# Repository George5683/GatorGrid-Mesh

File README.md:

# GatorGrid

GatorGrid is a multifunctional software solution designed for the Raspberry Pi Pico W by UF students to create a mesh network with wireless communication. It provides a low-cost, open-source alternative to existing mesh network solutions like ESP-WIFI-MESH and Zigbee by enabling seamless Wi-Fi-based communication between multiple nodes. The design uses two Pico W's per node in the network The project aims to ensure reliable message relay, even in case of node failures, making it ideal for individuals and organizations needing decentralized communication in remote or disaster-affected areas. GatorGrid focuses on accessibility, scalability, and real-time data transmission.

## Features
- MeshNode library for STA and AP mode
- Doxygen for documentation
- UART interaction for internode communication
- Kicad Custom PCB deisgn with external battery charging capabilities
- Network tree based creation from designated root node

## Requirements to run
- Install doxygen
- Install graphviz
- Install extensions for VS code if applicable: Doxygen Documentation Generator 

## How to run Doxygen
1. Use doxygen Doxyfile to generate the documentation
2. Use **start doc\html\index.html** (WINDOWS ONLY) or **open doc/html/index.html** (LINUX/MAC)

## How to upload code to PICO W's
1. Push the bootsel and plug the microcontroller into the computer
2. Create the .uf2 file and upload it to PICO W by dragging it into the directory

# PCB
The PCB is deisgned to have two Pico W's connected to each of the two vertical slots.

## Bugs:
- At the moment if in an environment with high congestion, packets may not arrive. Moving locations is required.
- SPI has a slight delay of 110 ms per message sent. 

## Author
George Salomon, Cole Smith, Jonathon Brown, Mateo Slivka, Maxwell Evans

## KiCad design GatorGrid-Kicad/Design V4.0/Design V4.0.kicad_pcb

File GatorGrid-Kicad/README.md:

## Kicad Designs

Design are separated into versions based on functionality and Design stages 

*Starting from BETA BUILD the first design V(X.0) is always the dev kit with extra Pico pinouts sockets for monitoring*

# Kicad Stages      
- INITIAL BUILD (V0.1 & V1.0)
- ALPHA BUILD (V2.0+)
- BETA BUILD (V3.0+)
- FINAL BUILD (V4.0+)

# External Sensor
At the moment the external sensor list is limited but can be expanded as needed
- DHT11 external PCB extension

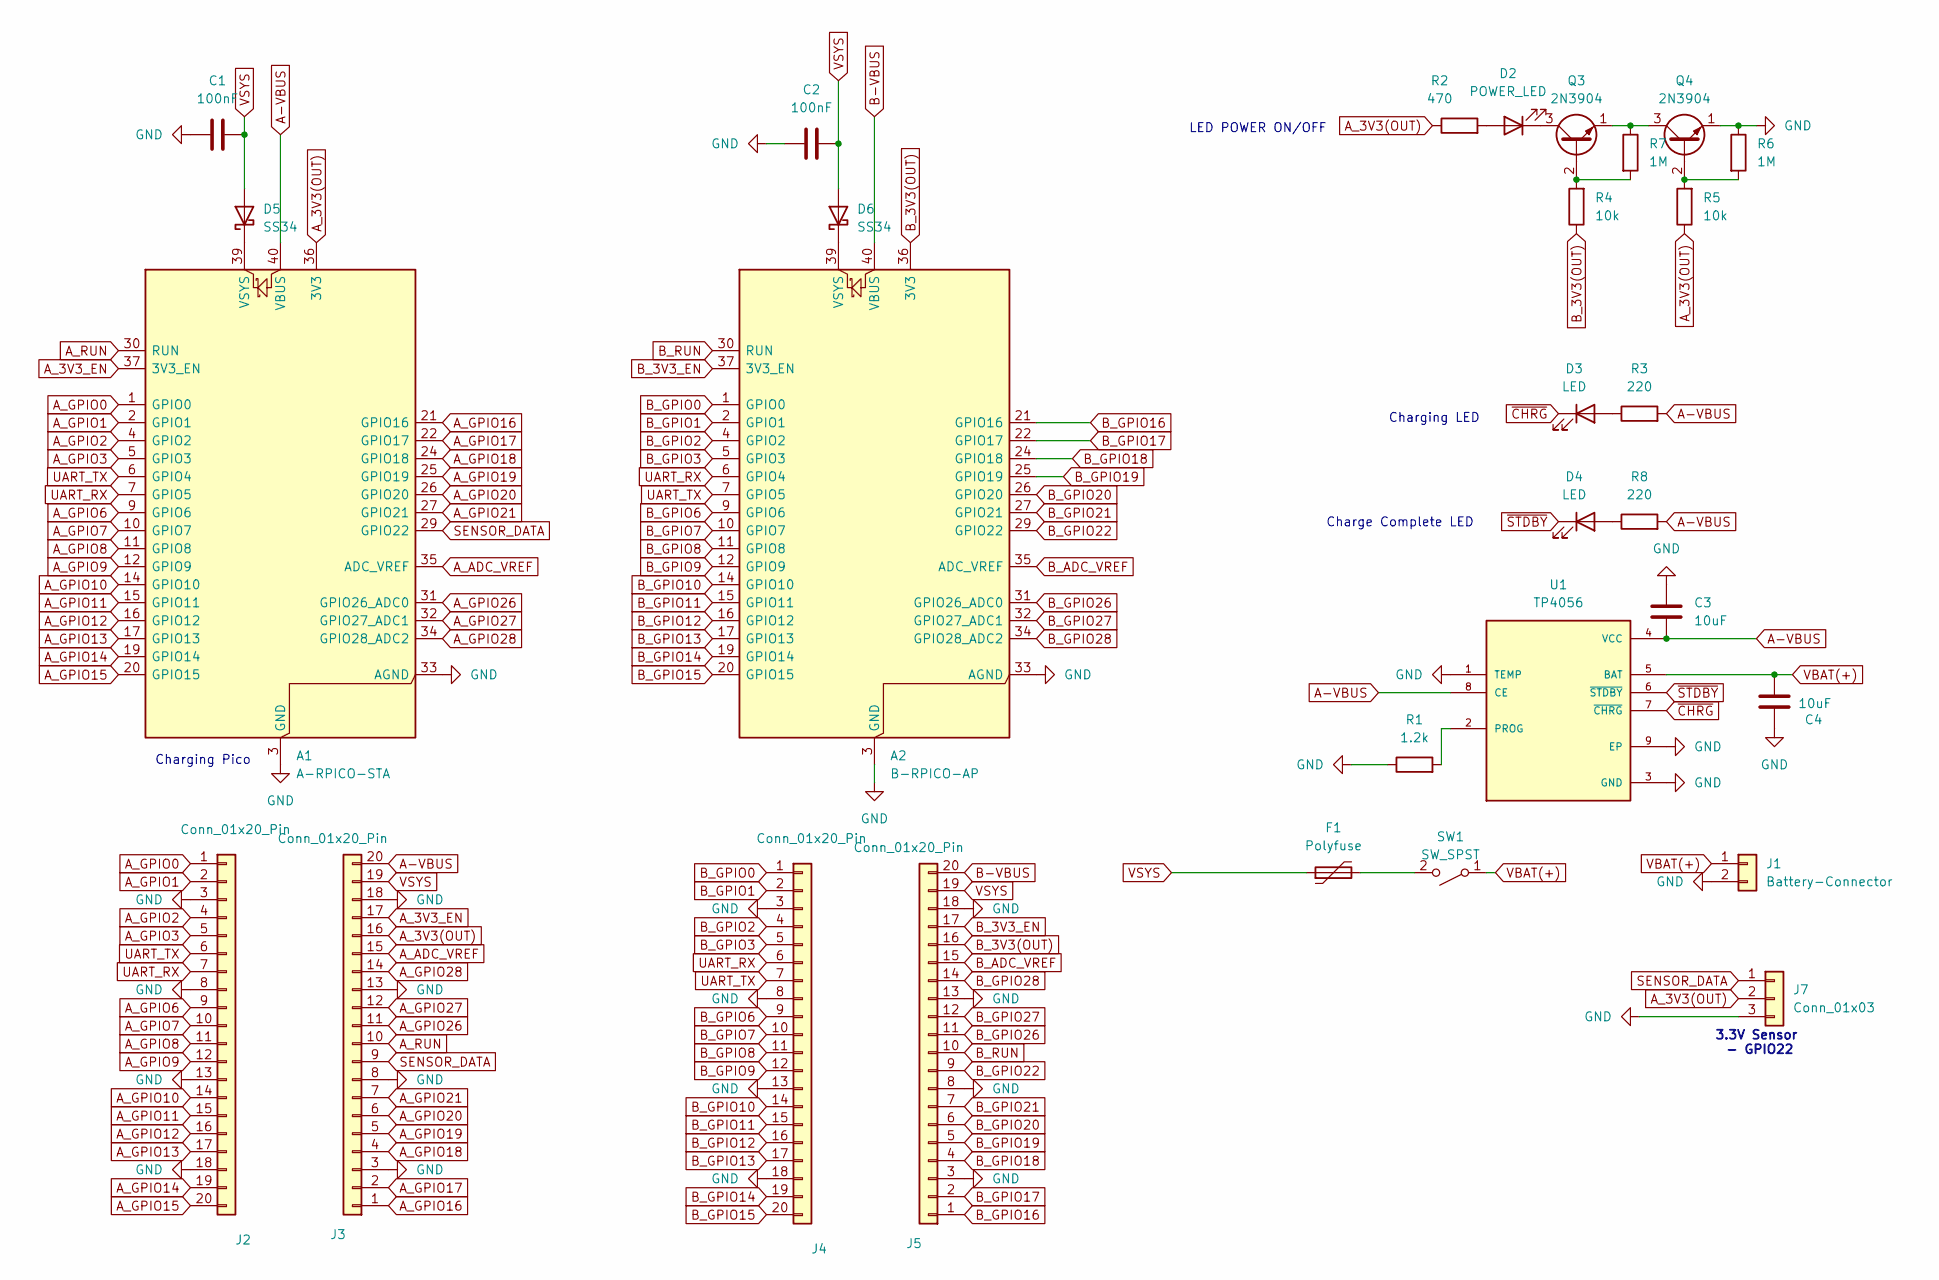
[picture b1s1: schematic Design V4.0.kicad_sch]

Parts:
A1: A-RPICO-STA; RaspberryPi_Pico_Common_THT
A2: B-RPICO-AP; RaspberryPi_Pico_Common_THT
C1, C2: 100nF; C_Disc_D5.0mm_W2.5mm_P2.50mm
C3, C4: 10uF; C_Radial_D5.0mm_H11.0mm_P2.00mm
D2: POWER_LED; LED_D5.0mm
D3, D4: LED; LED_D5.0mm
D5, D6: SS34; D_DO-41_SOD81_P7.62mm_Horizontal
F1: Polyfuse; Fuse_BelFuse_0ZRE0005FF_L8.3mm_W3.8mm
J1: Battery-Connector; JST_PH_S2B-PH-K_1x02_P2.00mm_Horizontal
J2, J3, J4, J5: Conn_01x20_Pin; PinSocket_1x20_P2.54mm_Vertical
J7: Conn_01x03; JST_XH_S3B-XH-A_1x03_P2.50mm_Horizontal
Q3, Q4: 2N3904; TO-92_Inline
R1: 1.2k; R_Axial_DIN0207_L6.3mm_D2.5mm_P7.62mm_Horizontal
R2: 470; R_Axial_DIN0207_L6.3mm_D2.5mm_P7.62mm_Horizontal
R3, R8: 220; R_Axial_DIN0207_L6.3mm_D2.5mm_P7.62mm_Horizontal
R4, R5: 10k; R_Axial_DIN0207_L6.3mm_D2.5mm_P7.62mm_Horizontal
R6, R7: 1M; R_Axial_DIN0207_L6.3mm_D2.5mm_P7.62mm_Horizontal
SW1: SW_SPST; SW_Slide_SPDT_Angled_CK_OS102011MA1Q
U1: TP4056; SOP127P600X175-9N

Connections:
A-VBUS: A1.40 (VBUS), C3.2, J3.20, R3.2, R8.2, U1.4 (VCC), U1.8 (CE)
A_3V3(OUT): A1.36 (3V3), J3.16, J7.2, R2.1, R5.1
A_3V3_EN: A1.37 (3V3_EN), J3.17
A_ADC_VREF: A1.35 (ADC_VREF), J3.15
A_GPIO0: A1.1 (GPIO0), J2.1
A_GPIO1: A1.2 (GPIO1), J2.2
A_GPIO2: A1.4 (GPIO2), J2.4
A_GPIO3: A1.5 (GPIO3), J2.5
A_GPIO6: A1.9 (GPIO6), J2.9
A_GPIO7: A1.10 (GPIO7), J2.10
A_GPIO8: A1.11 (GPIO8), J2.11
A_GPIO9: A1.12 (GPIO9), J2.12
A_GPIO10: A1.14 (GPIO10), J2.14
A_GPIO11: A1.15 (GPIO11), J2.15
A_GPIO12: A1.16 (GPIO12), J2.16
A_GPIO13: A1.17 (GPIO13), J2.17
A_GPIO14: A1.19 (GPIO14), J2.19
A_GPIO15: A1.20 (GPIO15), J2.20
A_GPIO16: A1.21 (GPIO16), J3.1
A_GPIO17: A1.22 (GPIO17), J3.2
A_GPIO18: A1.24 (GPIO18), J3.4
A_GPIO19: A1.25 (GPIO19), J3.5
A_GPIO20: A1.26 (GPIO20), J3.6
A_GPIO21: A1.27 (GPIO21), J3.7
A_GPIO26: A1.31 (GPIO26_ADC0), J3.11
A_GPIO27: A1.32 (GPIO27_ADC1), J3.12
A_GPIO28: A1.34 (GPIO28_ADC2), J3.14
A_RUN: A1.30 (RUN), J3.10
B-VBUS: A2.40 (VBUS), J5.20
B_3V3(OUT): A2.36 (3V3), J5.16, R4.1
B_3V3_EN: A2.37 (3V3_EN), J5.17
B_ADC_VREF: A2.35 (ADC_VREF), J5.15
B_GPIO0: A2.1 (GPIO0), J4.1
B_GPIO1: A2.2 (GPIO1), J4.2
B_GPIO2: A2.4 (GPIO2), J4.4
B_GPIO3: A2.5 (GPIO3), J4.5
B_GPIO6: A2.9 (GPIO6), J4.9
B_GPIO7: A2.10 (GPIO7), J4.10
B_GPIO8: A2.11 (GPIO8), J4.11
B_GPIO9: A2.12 (GPIO9), J4.12
B_GPIO10: A2.14 (GPIO10), J4.14
B_GPIO11: A2.15 (GPIO11), J4.15
B_GPIO12: A2.16 (GPIO12), J4.16
B_GPIO13: A2.17 (GPIO13), J4.17
B_GPIO14: A2.19 (GPIO14), J4.19
B_GPIO15: A2.20 (GPIO15), J4.20
B_GPIO16: A2.21 (GPIO16), J5.1
B_GPIO17: A2.22 (GPIO17), J5.2
B_GPIO18: A2.24 (GPIO18), J5.4
B_GPIO19: A2.25 (GPIO19), J5.5
B_GPIO20: A2.26 (GPIO20), J5.6
B_GPIO21: A2.27 (GPIO21), J5.7
B_GPIO22: A2.29 (GPIO22), J5.9
B_GPIO26: A2.31 (GPIO26_ADC0), J5.11
B_GPIO27: A2.32 (GPIO27_ADC1), J5.12
B_GPIO28: A2.34 (GPIO28_ADC2), J5.14
B_RUN: A2.30 (RUN), J5.10
GND: A1.3 (GND), A1.8 (GND), A1.13 (GND), A1.18 (GND), A1.23 (GND), A1.28 (GND), A1.33 (AGND), A1.38 (GND), A2.3 (GND), A2.8 (GND), A2.13 (GND), A2.18 (GND), A2.23 (GND), A2.28 (GND), A2.33 (AGND), A2.38 (GND), C1.2, C2.1, C3.1, C4.1, J1.2, J2.3, J2.8, J2.13, J2.18, J3.3, J3.8, J3.13, J3.18, J4.3, J4.8, J4.13, J4.18, J5.3, J5.8, J5.13, J5.18, J7.3, Q4.1 (E), R1.1, R6.1, U1.1 (TEMP), U1.3 (GND), U1.9 (EP)
unnamed: A1.39 (VSYS), D5.1 (K)
unnamed: A2.39 (VSYS), D6.1 (K)
unnamed: D2.2 (A), R2.2
unnamed: D2.1 (K), Q3.3 (C)
unnamed: D3.2 (A), R3.1
unnamed: D4.2 (A), R8.1
unnamed: Q3.2 (B), R4.2, R7.2
unnamed: Q3.1 (E), Q4.3 (C), R7.1
unnamed: Q4.2 (B), R5.2, R6.2
unnamed: F1.2, SW1.2 (B)
unnamed: R1.2, U1.2 (PROG)
SENSOR_DATA: A1.29 (GPIO22), J3.9, J7.1
UART_RX: A1.7 (GPIO5), A2.6 (GPIO4), J2.7, J4.6
UART_TX: A1.6 (GPIO4), A2.7 (GPIO5), J2.6, J4.7
VBAT(+): C4.2, J1.1, SW1.1 (A), U1.5 (BAT)
VSYS: C1.1, C2.2, D5.2 (A), D6.2 (A), F1.1, J3.19, J5.19
~CHRG: D3.1 (K), U1.7 (~CHRG)
~STDBY: D4.1 (K), U1.6 (~STDBY)

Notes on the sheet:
Charging Pico
Charge Complete LED
3.3V Sensor - GPIO22
LED POWER ON/OFF
Charging LED

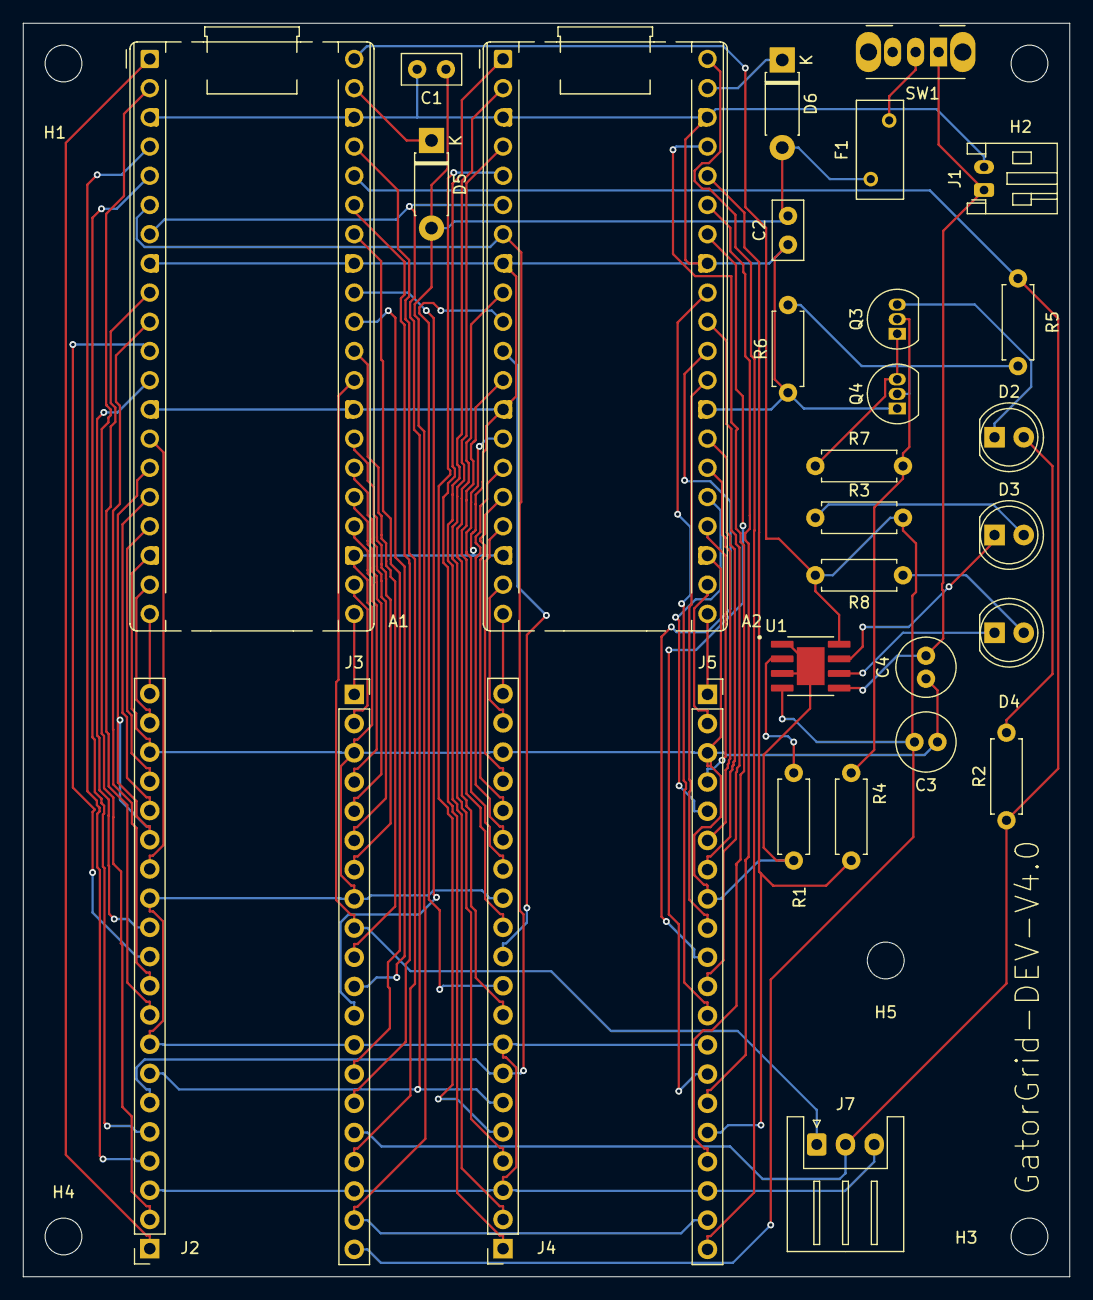
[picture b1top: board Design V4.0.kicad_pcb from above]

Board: 2 copper layers, 91.0 x 109.0 mm, 35 parts (0 on the bottom side), 76 nets.

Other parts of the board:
H1, H2, H3, H4, H5: MountingHole_3.2mm_M3_ISO7380

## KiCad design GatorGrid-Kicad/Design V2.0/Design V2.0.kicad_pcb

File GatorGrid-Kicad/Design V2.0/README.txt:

# Kicad Design V2.0

## Explanation for the Pinouts on the Pico W:

- GPIO 1-22 and 26-28 are as the schematic states
- VBUS is 5V when connected to micro usb to power the Pico
- VSYS can power the Pico with ~1.8-5.5V input

## Schematic Update:
- Fixed wiring of temp on the TP4056 as it was disconnected which casued the battery to not charge. 
- Changed POWER LED to be driven by two transistors which allows it to turn on when both picos are on. 
- Removed the schottky diode connected to the battery and instead put a diode on each VSYS out from each pico in order to prevent backflow when eitehr are plugged in as VSYS can be input and output. 
- Reworked Wiring on PCB

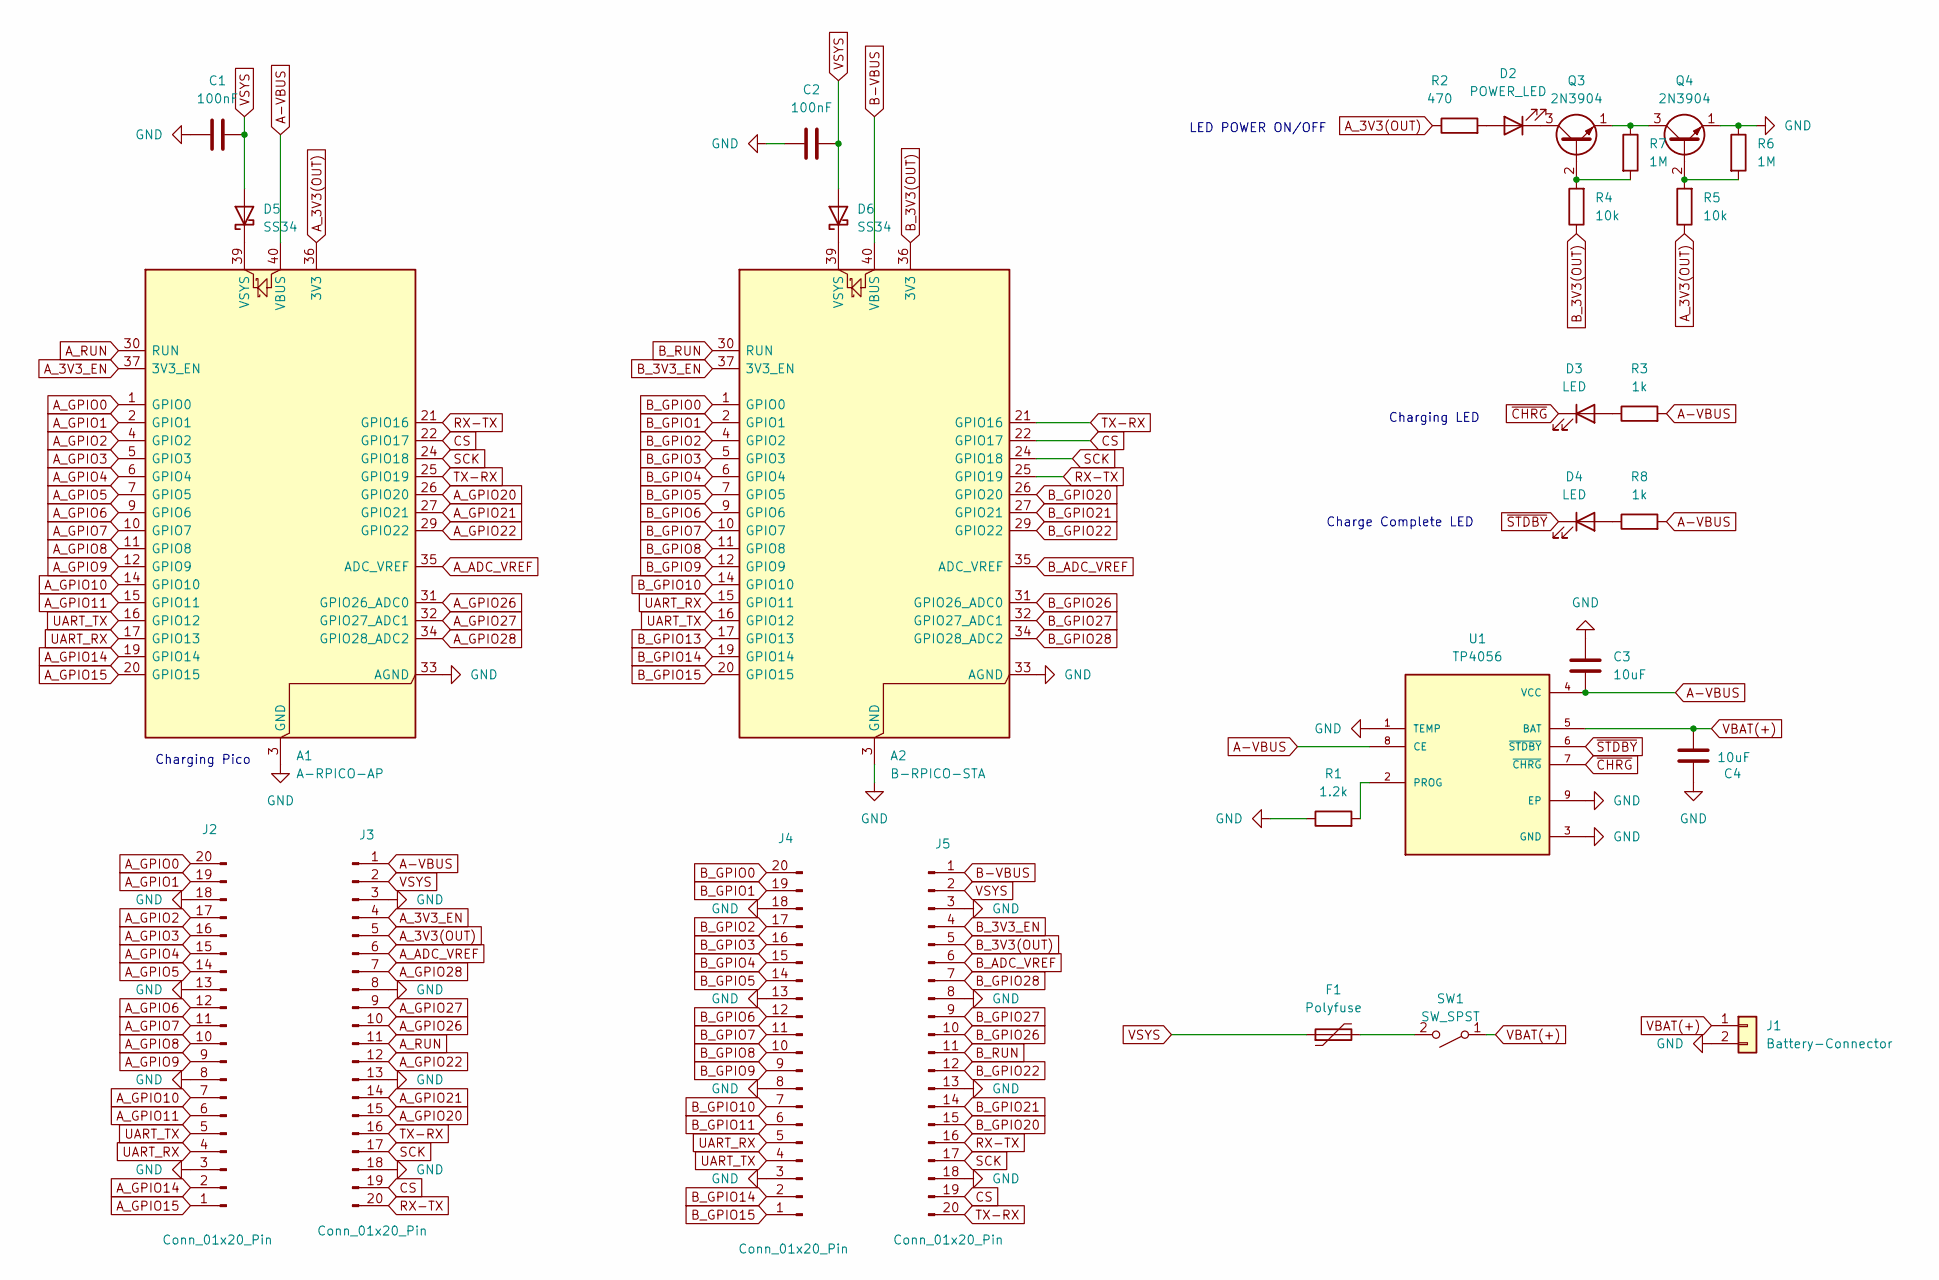
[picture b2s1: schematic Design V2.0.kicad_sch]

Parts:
A1: A-RPICO-AP; RaspberryPi_Pico_Common_THT
A2: B-RPICO-STA; RaspberryPi_Pico_Common_THT
C1, C2: 100nF; C_Disc_D5.0mm_W2.5mm_P2.50mm
C3, C4: 10uF; C_Radial_D5.0mm_H11.0mm_P2.00mm
D2: POWER_LED; LED_D5.0mm
D3, D4: LED; LED_D5.0mm
D5, D6: SS34; D_DO-41_SOD81_P7.62mm_Horizontal
F1: Polyfuse; Fuse_BelFuse_0ZRE0005FF_L8.3mm_W3.8mm
J1: Battery-Connector; JST_PH_S2B-PH-K_1x02_P2.00mm_Horizontal
J2, J3, J4, J5: Conn_01x20_Pin; PinSocket_1x20_P2.54mm_Vertical
Q3, Q4: 2N3904; TO-92_Inline
R1: 1.2k; R_Axial_DIN0207_L6.3mm_D2.5mm_P7.62mm_Horizontal
R2: 470; R_Axial_DIN0207_L6.3mm_D2.5mm_P7.62mm_Horizontal
R3, R8: 1k; R_Axial_DIN0207_L6.3mm_D2.5mm_P7.62mm_Horizontal
R4, R5: 10k; R_Axial_DIN0207_L6.3mm_D2.5mm_P7.62mm_Horizontal
R6, R7: 1M; R_Axial_DIN0207_L6.3mm_D2.5mm_P7.62mm_Horizontal
SW1: SW_SPST; SW_Slide_SPDT_Angled_CK_OS102011MA1Q
U1: TP4056; SOP127P600X175-9N

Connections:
A-VBUS: A1.40 (VBUS), C3.2, J3.1, R3.2, R8.2, U1.4 (VCC), U1.8 (CE)
A_3V3(OUT): A1.36 (3V3), J3.5, R2.1, R5.1
A_3V3_EN: A1.37 (3V3_EN), J3.4
A_ADC_VREF: A1.35 (ADC_VREF), J3.6
A_GPIO0: A1.1 (GPIO0), J2.20
A_GPIO1: A1.2 (GPIO1), J2.19
A_GPIO2: A1.4 (GPIO2), J2.17
A_GPIO3: A1.5 (GPIO3), J2.16
A_GPIO4: A1.6 (GPIO4), J2.15
A_GPIO5: A1.7 (GPIO5), J2.14
A_GPIO6: A1.9 (GPIO6), J2.12
A_GPIO7: A1.10 (GPIO7), J2.11
A_GPIO8: A1.11 (GPIO8), J2.10
A_GPIO9: A1.12 (GPIO9), J2.9
A_GPIO10: A1.14 (GPIO10), J2.7
A_GPIO11: A1.15 (GPIO11), J2.6
A_GPIO14: A1.19 (GPIO14), J2.2
A_GPIO15: A1.20 (GPIO15), J2.1
A_GPIO20: A1.26 (GPIO20), J3.15
A_GPIO21: A1.27 (GPIO21), J3.14
A_GPIO22: A1.29 (GPIO22), J3.12
A_GPIO26: A1.31 (GPIO26_ADC0), J3.10
A_GPIO27: A1.32 (GPIO27_ADC1), J3.9
A_GPIO28: A1.34 (GPIO28_ADC2), J3.7
A_RUN: A1.30 (RUN), J3.11
B-VBUS: A2.40 (VBUS), J5.1
B_3V3(OUT): A2.36 (3V3), J5.5, R4.1
B_3V3_EN: A2.37 (3V3_EN), J5.4
B_ADC_VREF: A2.35 (ADC_VREF), J5.6
B_GPIO0: A2.1 (GPIO0), J4.20
B_GPIO1: A2.2 (GPIO1), J4.19
B_GPIO2: A2.4 (GPIO2), J4.17
B_GPIO3: A2.5 (GPIO3), J4.16
B_GPIO4: A2.6 (GPIO4), J4.15
B_GPIO5: A2.7 (GPIO5), J4.14
B_GPIO6: A2.9 (GPIO6), J4.12
B_GPIO7: A2.10 (GPIO7), J4.11
B_GPIO8: A2.11 (GPIO8), J4.10
B_GPIO9: A2.12 (GPIO9), J4.9
B_GPIO10: A2.14 (GPIO10), J4.7
B_GPIO11: J4.6
B_GPIO13: A2.17 (GPIO13)
B_GPIO14: A2.19 (GPIO14), J4.2
B_GPIO15: A2.20 (GPIO15), J4.1
B_GPIO20: A2.26 (GPIO20), J5.15
B_GPIO21: A2.27 (GPIO21), J5.14
B_GPIO22: A2.29 (GPIO22), J5.12
B_GPIO26: A2.31 (GPIO26_ADC0), J5.10
B_GPIO27: A2.32 (GPIO27_ADC1), J5.9
B_GPIO28: A2.34 (GPIO28_ADC2), J5.7
B_RUN: A2.30 (RUN), J5.11
CS: A1.22 (GPIO17), A2.22 (GPIO17), J3.19, J5.19
GND: A1.3 (GND), A1.8 (GND), A1.13 (GND), A1.18 (GND), A1.23 (GND), A1.28 (GND), A1.33 (AGND), A1.38 (GND), A2.3 (GND), A2.8 (GND), A2.13 (GND), A2.18 (GND), A2.23 (GND), A2.28 (GND), A2.33 (AGND), A2.38 (GND), C1.2, C2.1, C3.1, C4.1, J1.2, J2.3, J2.8, J2.13, J2.18, J3.3, J3.8, J3.13, J3.18, J4.3, J4.8, J4.13, J4.18, J5.3, J5.8, J5.13, J5.18, Q4.1 (E), R1.1, R6.1, U1.1 (TEMP), U1.3 (GND), U1.9 (EP)
unnamed: A1.39 (VSYS), D5.1 (K)
unnamed: A2.39 (VSYS), D6.1 (K)
unnamed: D2.2 (A), R2.2
unnamed: D2.1 (K), Q3.3 (C)
unnamed: D3.2 (A), R3.1
unnamed: D4.2 (A), R8.1
unnamed: Q3.2 (B), R4.2, R7.2
unnamed: Q3.1 (E), Q4.3 (C), R7.1
unnamed: Q4.2 (B), R5.2, R6.2
unnamed: F1.2, SW1.2 (B)
unnamed: R1.2, U1.2 (PROG)
RX-TX: A1.21 (GPIO16), A2.25 (GPIO19), J3.20, J5.16
SCK: A1.24 (GPIO18), A2.24 (GPIO18), J3.17, J5.17
TX-RX: A1.25 (GPIO19), A2.21 (GPIO16), J3.16, J5.20
UART_RX: A1.17 (GPIO13), A2.15 (GPIO11), J2.4, J4.5
UART_TX: A1.16 (GPIO12), A2.16 (GPIO12), J2.5, J4.4
VBAT(+): C4.2, J1.1, SW1.1 (A), U1.5 (BAT)
VSYS: C1.1, C2.2, D5.2 (A), D6.2 (A), F1.1, J3.2, J5.2
~CHRG: D3.1 (K), U1.7 (~CHRG)
~STDBY: D4.1 (K), U1.6 (~STDBY)

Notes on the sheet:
Charging Pico
Charge Complete LED
LED POWER ON/OFF
Charging LED

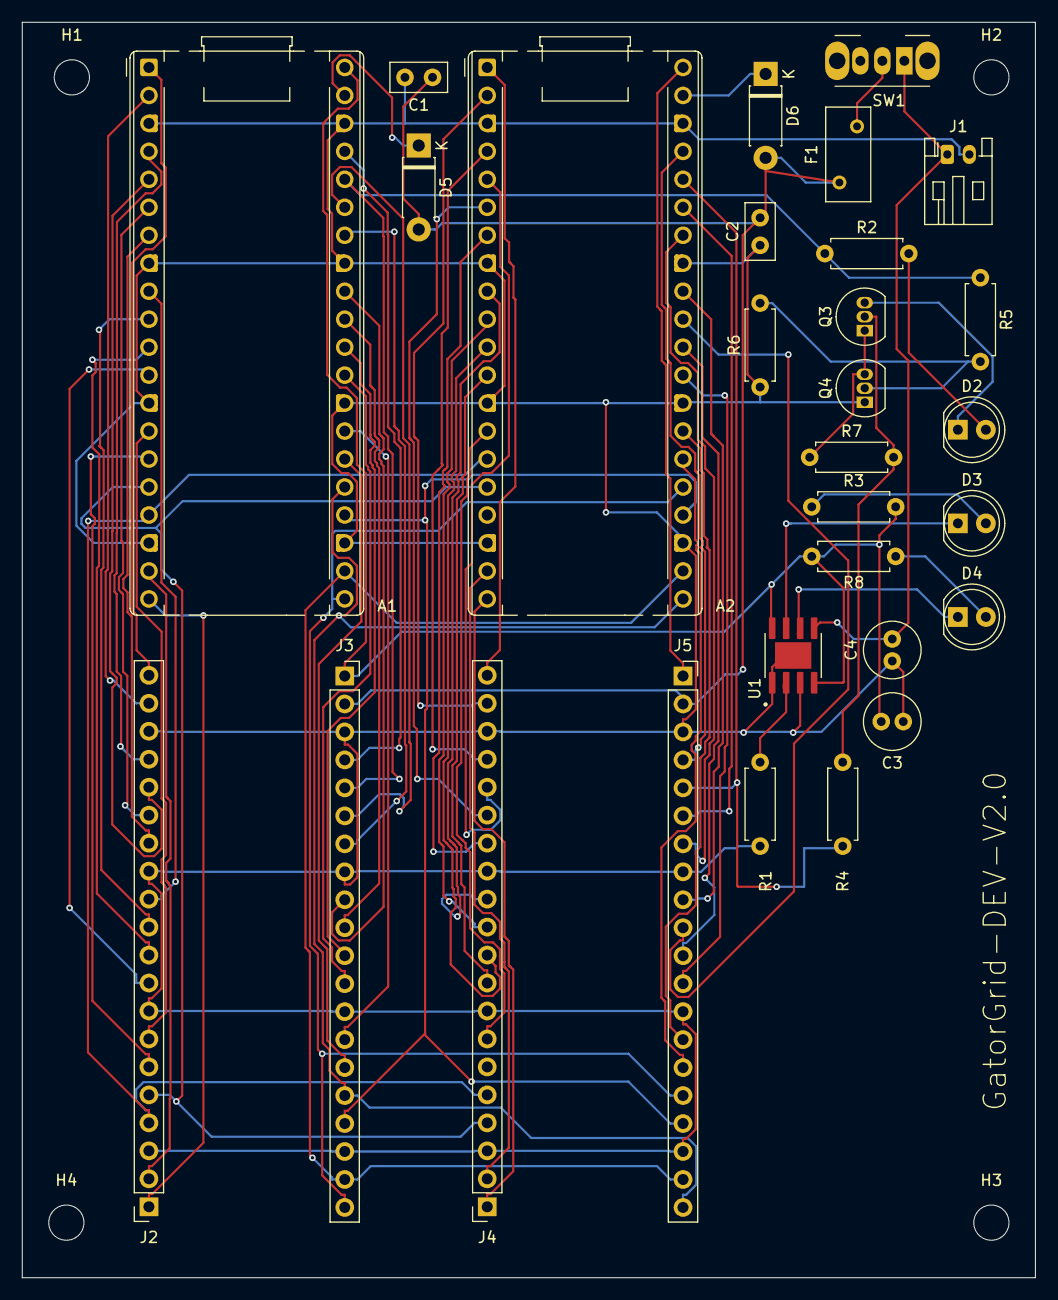
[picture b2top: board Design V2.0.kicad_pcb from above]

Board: 2 copper layers, 92.0 x 114.0 mm, 33 parts (0 on the bottom side), 71 nets.

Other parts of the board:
H1, H2, H3, H4: MountingHole_3.2mm_M3_ISO7380

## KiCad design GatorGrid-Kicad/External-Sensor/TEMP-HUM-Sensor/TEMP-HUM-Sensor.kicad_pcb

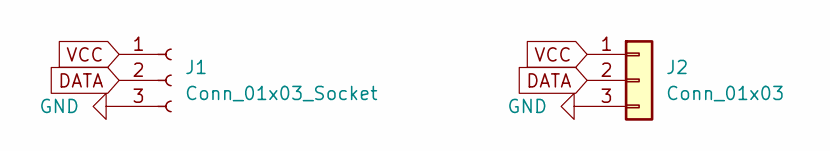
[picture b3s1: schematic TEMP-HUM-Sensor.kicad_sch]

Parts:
J1: Conn_01x03_Socket; PinSocket_1x03_P2.54mm_Vertical
J2: Conn_01x03; JST_XH_S3B-XH-A_1x03_P2.50mm_Horizontal

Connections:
DATA: J1.2, J2.2
GND: J1.3, J2.3
VCC: J1.1, J2.1

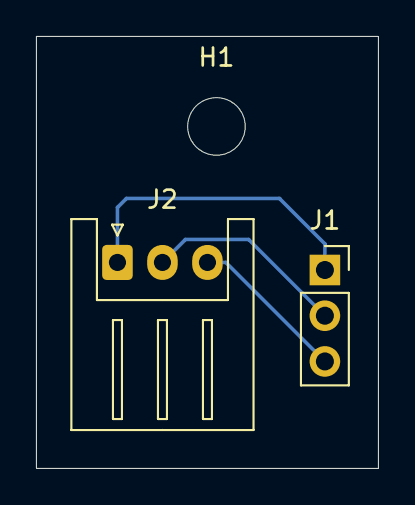
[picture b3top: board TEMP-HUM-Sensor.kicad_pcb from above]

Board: 2 copper layers, 19.0 x 24.0 mm, 3 parts (0 on the bottom side), 3 nets.

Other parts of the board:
H1: MountingHole_3.2mm_M3_ISO7380

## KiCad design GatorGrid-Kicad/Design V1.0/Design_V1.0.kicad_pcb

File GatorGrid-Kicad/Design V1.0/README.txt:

# Kicad Design V1.0

## Explanation for the Pinouts on the Pico W:

- GPIO 1-22 and 26-28 are as the schematic states
- VBUS is 5V when connected to micro usb to power the Pico
- VSYS can power the Pico with ~1.8-5.5V input

## Schematic Update:
- Added a JST connector for an extenal battery to be connected
- Added a switch after the JSt conncector for powering the Picos
- Added a polyfuse (polyfuse's reset instead of replacing the fuse if its broken)
- Added a Schottky diode (to prevent current backflow and if user connects the battery backwards)
- Added a charging/safety cicuit [TP4056] (for charging the battery and battery management)

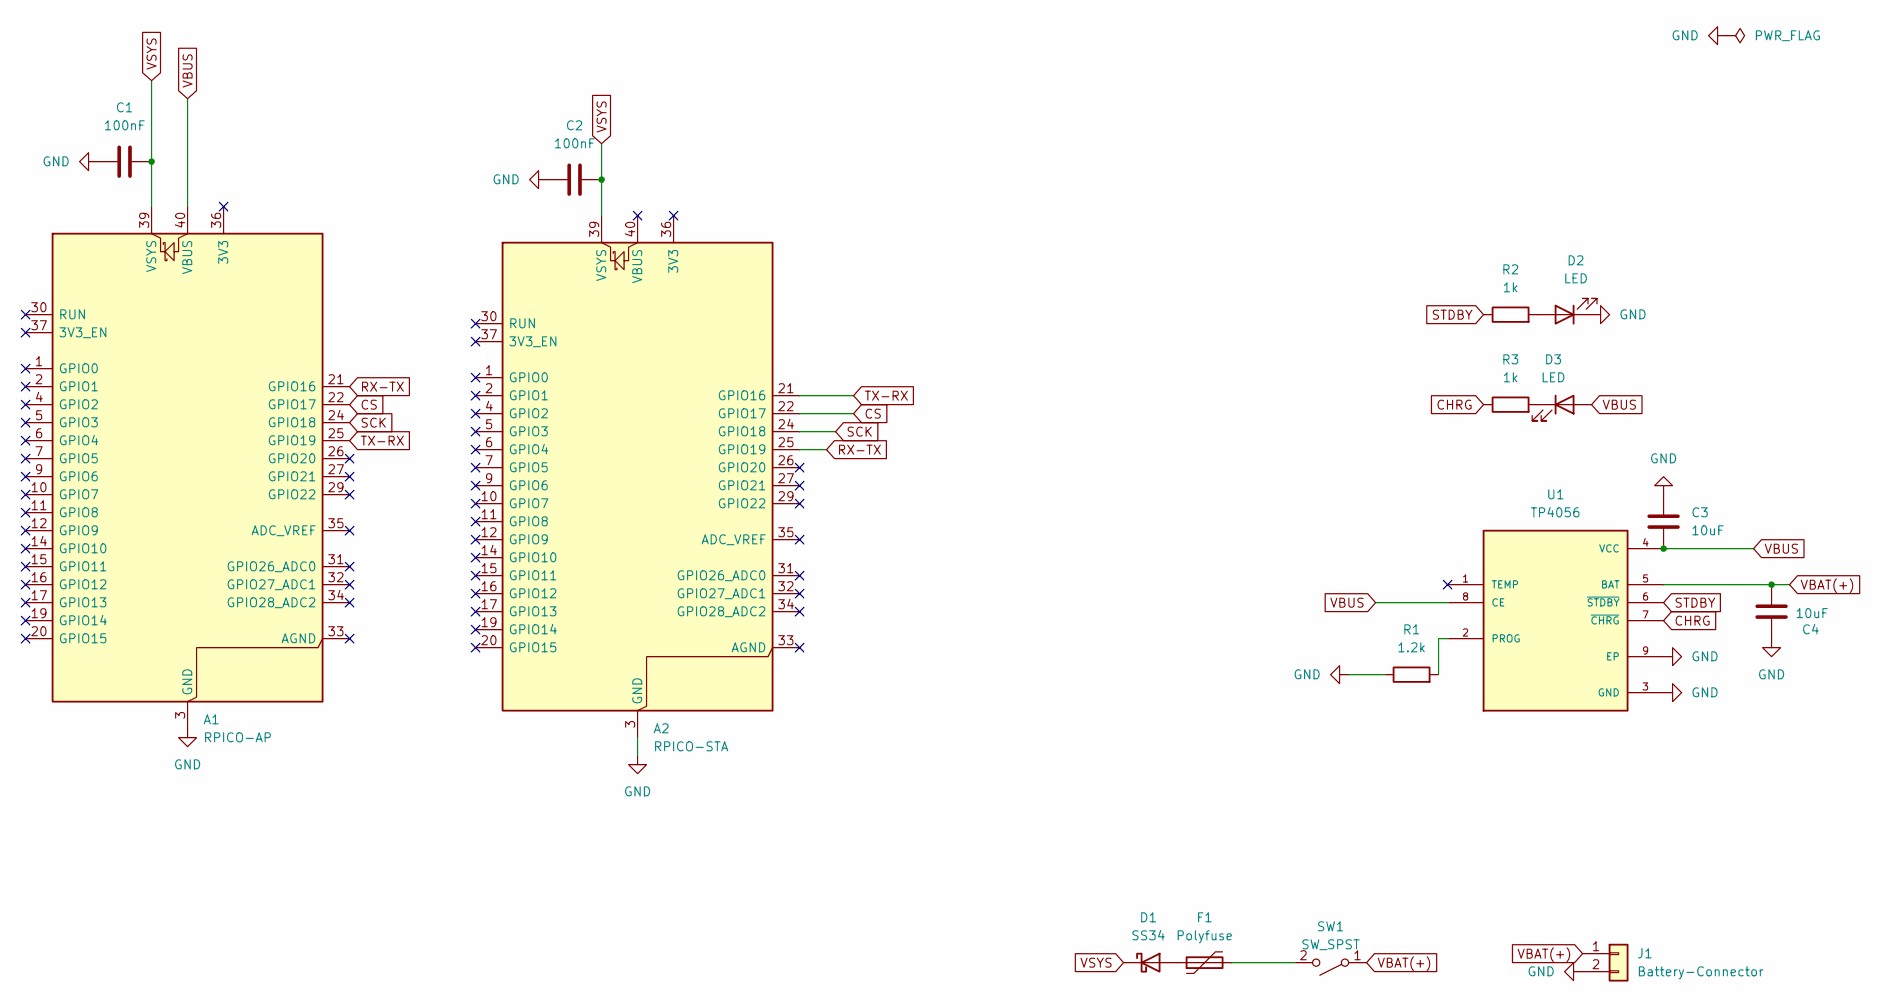
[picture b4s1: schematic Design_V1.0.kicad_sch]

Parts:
A1: RPICO-AP; RaspberryPi_Pico_Common_THT
A2: RPICO-STA; RaspberryPi_Pico_Common_THT
C1, C2: 100nF; C_Disc_D5.0mm_W2.5mm_P2.50mm
C3, C4: 10uF; C_Radial_D5.0mm_H11.0mm_P2.00mm
D1: SS34; D_DO-41_SOD81_P7.62mm_Horizontal
D2, D3: LED; LED_D5.0mm
F1: Polyfuse; Fuse_BelFuse_0ZRE0005FF_L8.3mm_W3.8mm
J1: Battery-Connector; JST_PH_S2B-PH-K_1x02_P2.00mm_Horizontal
R1: 1.2k; R_Axial_DIN0207_L6.3mm_D2.5mm_P7.62mm_Horizontal
R2, R3: 1k; R_Axial_DIN0207_L6.3mm_D2.5mm_P7.62mm_Horizontal
SW1: SW_SPST; SW_Slide_SPDT_Angled_CK_OS102011MA1Q
U1: TP4056; SOP127P600X175-9N

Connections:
CHRG: R3.1, U1.7 (~CHRG)
CS: A1.22 (GPIO17), A2.22 (GPIO17)
GND: A1.3 (GND), A1.8 (GND), A1.13 (GND), A1.18 (GND), A1.23 (GND), A1.28 (GND), A1.38 (GND), A2.3 (GND), A2.8 (GND), A2.13 (GND), A2.18 (GND), A2.23 (GND), A2.28 (GND), A2.38 (GND), C1.2, C2.2, C3.1, C4.1, D2.1 (K), J1.2, R1.1, U1.3 (GND), U1.9 (EP)
unnamed: D1.2 (A), F1.1
unnamed: D2.2 (A), R2.2
unnamed: D3.1 (K), R3.2
unnamed: F1.2, SW1.2 (B)
unnamed: R1.2, U1.2 (PROG)
RX-TX: A1.21 (GPIO16), A2.25 (GPIO19)
SCK: A1.24 (GPIO18), A2.24 (GPIO18)
STDBY: R2.1, U1.6 (~STDBY)
TX-RX: A1.25 (GPIO19), A2.21 (GPIO16)
VBAT(+): C4.2, J1.1, SW1.1 (A), U1.5 (BAT)
VBUS: A1.40 (VBUS), C3.2, D3.2 (A), U1.4 (VCC), U1.8 (CE)
VSYS: A1.39 (VSYS), A2.39 (VSYS), C1.1, C2.1, D1.1 (K)

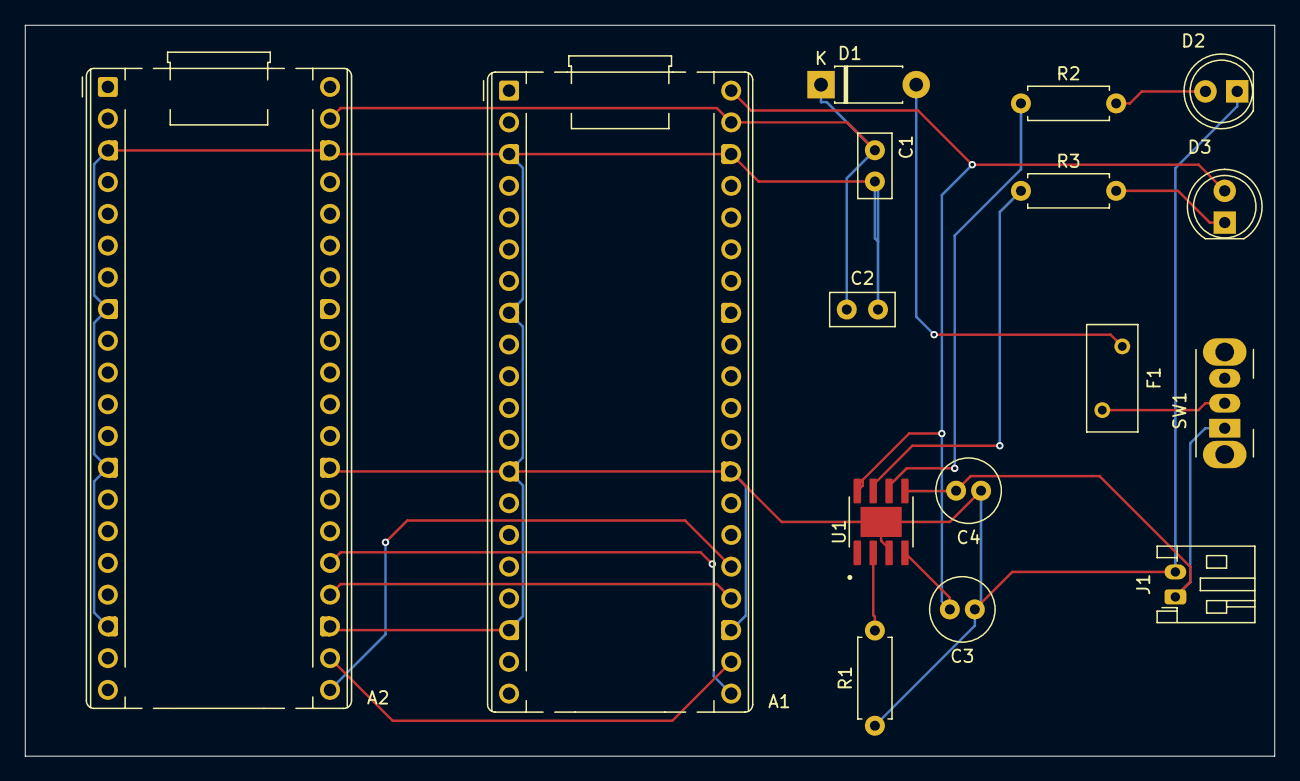
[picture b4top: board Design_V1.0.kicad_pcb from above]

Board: 2 copper layers, 100.0 x 58.5 mm, 16 parts (0 on the bottom side), 15 nets.

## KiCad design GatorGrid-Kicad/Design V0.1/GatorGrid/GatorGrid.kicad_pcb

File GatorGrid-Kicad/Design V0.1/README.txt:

## Kicad Design V0.1
Explanation for the Pinouts on the Pico W:

- GPIO 1-22 and 26-28 are as the schematic states
- VBUS is 5V when connected to micro usb to power the Pico
- VSYS can power the Pico with ~1.8-5.5V input

TIPS:
- For adding a secondary power source, you need a schottky diode on the VSYS

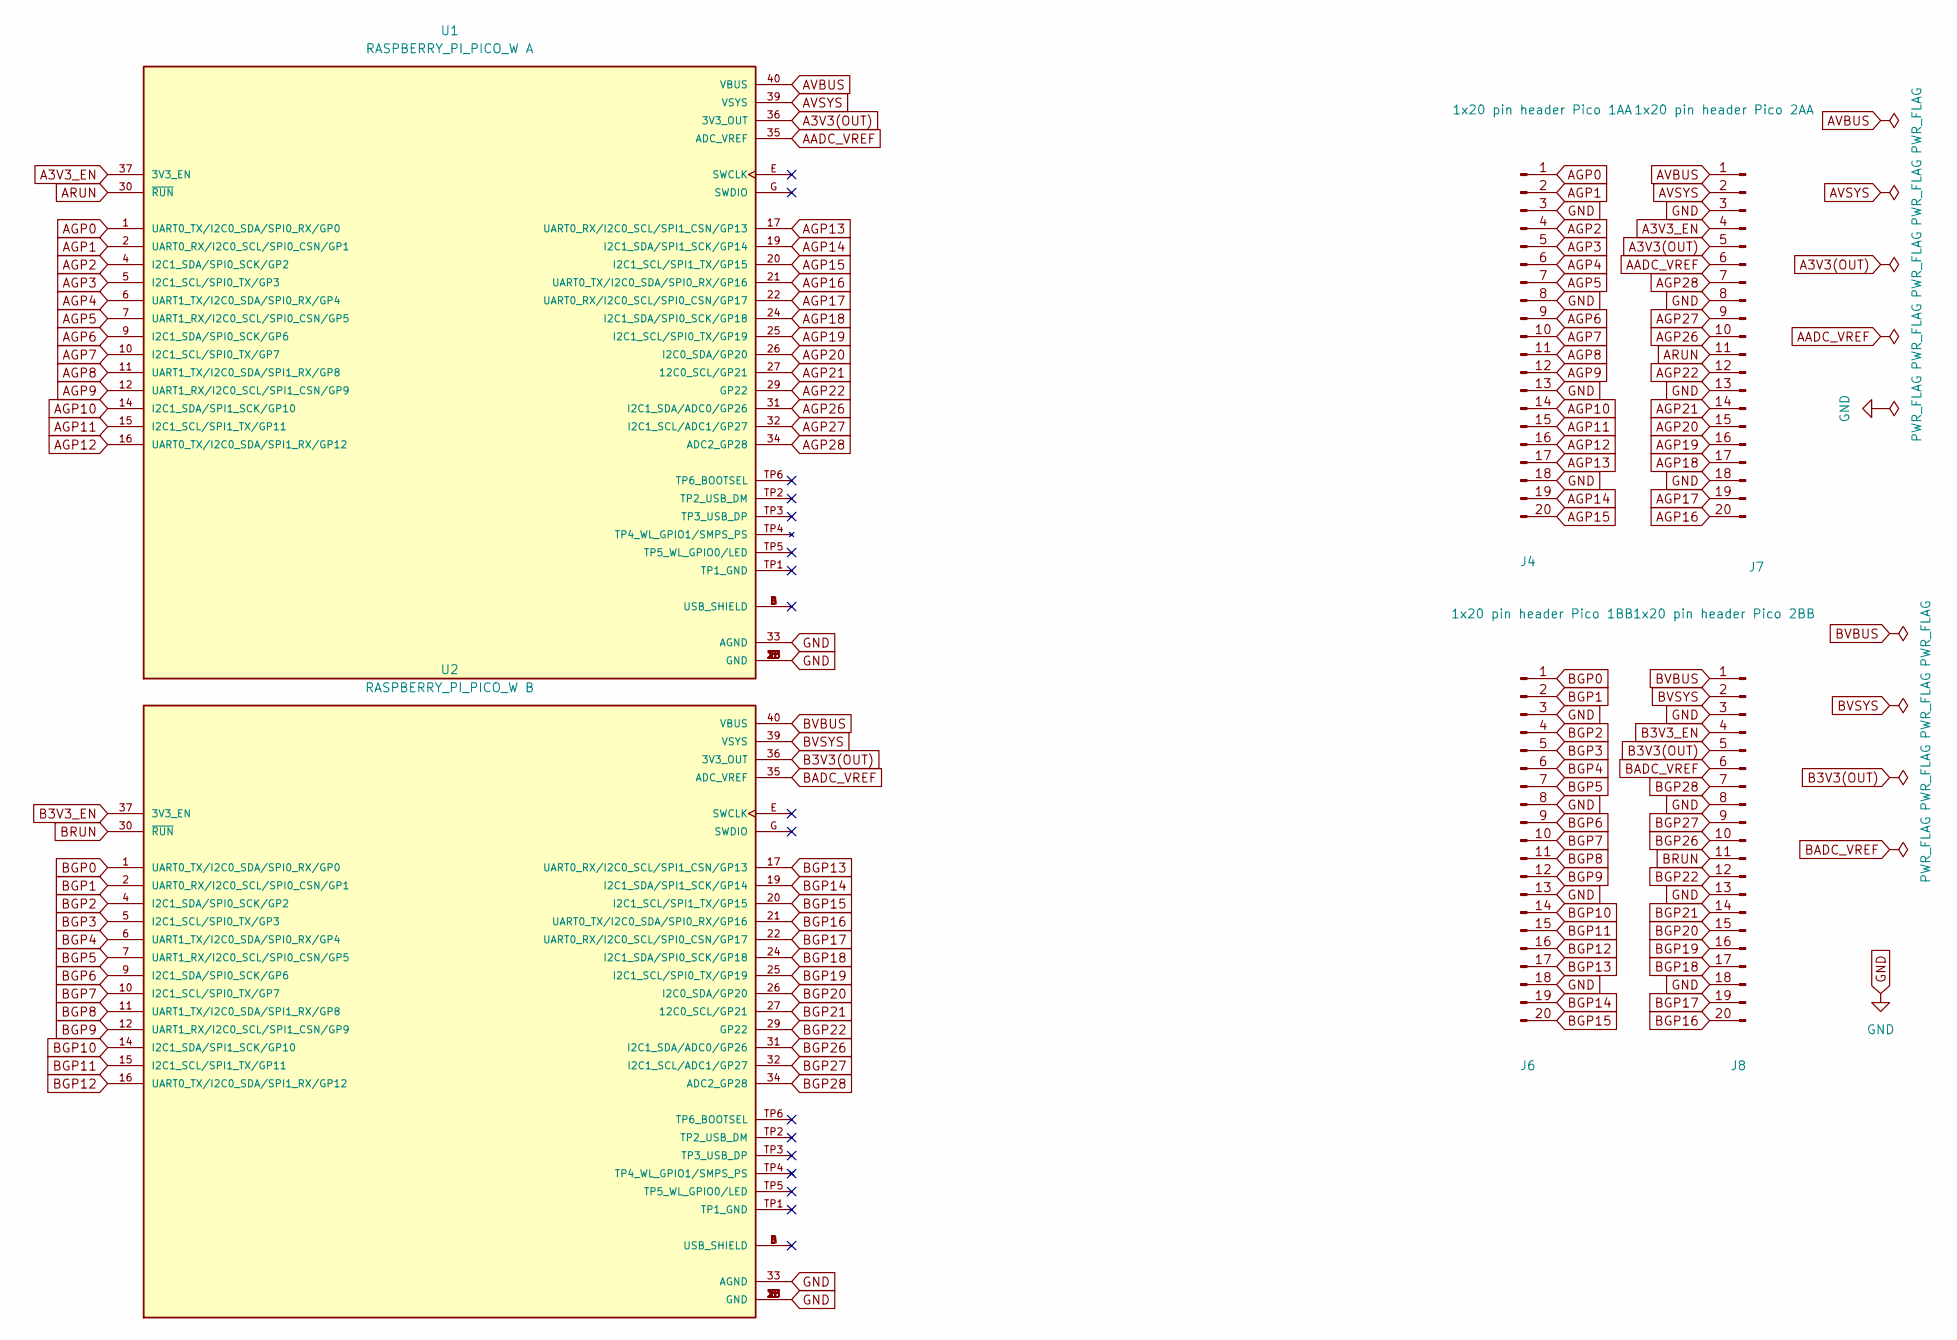
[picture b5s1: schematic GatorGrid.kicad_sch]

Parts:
J4: 1x20 pin header Pico 1AA; PinHeader_1x20_P2.54mm_Vertical
J6: 1x20 pin header Pico 1BB; PinHeader_1x20_P2.54mm_Vertical
J7: 1x20 pin header Pico 2AA; PinHeader_1x20_P2.54mm_Vertical
J8: 1x20 pin header Pico 2BB; PinHeader_1x20_P2.54mm_Vertical
U1: RASPBERRY_PI_PICO_W A; RaspberryPi_Pico_Common_THT; PARTREV 2.4
U2: RASPBERRY_PI_PICO_W B; RaspberryPi_Pico_Common_THT; PARTREV 2.4

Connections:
A3V3(OUT): J7.5, U1.36 (3V3_OUT)
A3V3_EN: J7.4, U1.37 (3V3_EN)
AADC_VREF: J7.6, U1.35 (ADC_VREF)
AGP0: J4.1, U1.1 (UART0_TX/I2C0_SDA/SPI0_RX/GP0)
AGP1: J4.2, U1.2 (UART0_RX/I2C0_SCL/SPI0_CSN/GP1)
AGP2: J4.4, U1.4 (I2C1_SDA/SPI0_SCK/GP2)
AGP3: J4.5, U1.5 (I2C1_SCL/SPI0_TX/GP3)
AGP4: J4.6, U1.6 (UART1_TX/I2C0_SDA/SPI0_RX/GP4)
AGP5: J4.7, U1.7 (UART1_RX/I2C0_SCL/SPI0_CSN/GP5)
AGP6: J4.9, U1.9 (I2C1_SDA/SPI0_SCK/GP6)
AGP7: J4.10, U1.10 (I2C1_SCL/SPI0_TX/GP7)
AGP8: J4.11, U1.11 (UART1_TX/I2C0_SDA/SPI1_RX/GP8)
AGP9: J4.12, U1.12 (UART1_RX/I2C0_SCL/SPI1_CSN/GP9)
AGP10: J4.14, U1.14 (I2C1_SDA/SPI1_SCK/GP10)
AGP11: J4.15, U1.15 (I2C1_SCL/SPI1_TX/GP11)
AGP12: J4.16, U1.16 (UART0_TX/I2C0_SDA/SPI1_RX/GP12)
AGP13: J4.17, U1.17 (UART0_RX/I2C0_SCL/SPI1_CSN/GP13)
AGP14: J4.19, U1.19 (I2C1_SDA/SPI1_SCK/GP14)
AGP15: J4.20, U1.20 (I2C1_SCL/SPI1_TX/GP15)
AGP16: J7.20, U1.21 (UART0_TX/I2C0_SDA/SPI0_RX/GP16)
AGP17: J7.19, U1.22 (UART0_RX/I2C0_SCL/SPI0_CSN/GP17)
AGP18: J7.17, U1.24 (I2C1_SDA/SPI0_SCK/GP18)
AGP19: J7.16, U1.25 (I2C1_SCL/SPI0_TX/GP19)
AGP20: J7.15, U1.26 (I2C0_SDA/GP20)
AGP21: J7.14, U1.27 (12C0_SCL/GP21)
AGP22: J7.12, U1.29 (GP22)
AGP26: J7.10, U1.31 (I2C1_SDA/ADC0/GP26)
AGP27: J7.9, U1.32 (I2C1_SCL/ADC1/GP27)
AGP28: J7.7, U1.34 (ADC2_GP28)
ARUN: J7.11, U1.30 (~RUN)
AVBUS: J7.1, U1.40 (VBUS)
AVSYS: J7.2, U1.39 (VSYS)
B3V3(OUT): J8.5, U2.36 (3V3_OUT)
B3V3_EN: J8.4, U2.37 (3V3_EN)
BADC_VREF: J8.6, U2.35 (ADC_VREF)
BGP0: J6.1, U2.1 (UART0_TX/I2C0_SDA/SPI0_RX/GP0)
BGP1: J6.2, U2.2 (UART0_RX/I2C0_SCL/SPI0_CSN/GP1)
BGP2: J6.4, U2.4 (I2C1_SDA/SPI0_SCK/GP2)
BGP3: J6.5, U2.5 (I2C1_SCL/SPI0_TX/GP3)
BGP4: J6.6, U2.6 (UART1_TX/I2C0_SDA/SPI0_RX/GP4)
BGP5: J6.7, U2.7 (UART1_RX/I2C0_SCL/SPI0_CSN/GP5)
BGP6: J6.9, U2.9 (I2C1_SDA/SPI0_SCK/GP6)
BGP7: J6.10, U2.10 (I2C1_SCL/SPI0_TX/GP7)
BGP8: J6.11, U2.11 (UART1_TX/I2C0_SDA/SPI1_RX/GP8)
BGP9: J6.12, U2.12 (UART1_RX/I2C0_SCL/SPI1_CSN/GP9)
BGP10: J6.14, U2.14 (I2C1_SDA/SPI1_SCK/GP10)
BGP11: J6.15, U2.15 (I2C1_SCL/SPI1_TX/GP11)
BGP12: J6.16, U2.16 (UART0_TX/I2C0_SDA/SPI1_RX/GP12)
BGP13: J6.17, U2.17 (UART0_RX/I2C0_SCL/SPI1_CSN/GP13)
BGP14: J6.19, U2.19 (I2C1_SDA/SPI1_SCK/GP14)
BGP15: J6.20, U2.20 (I2C1_SCL/SPI1_TX/GP15)
BGP16: J8.20, U2.21 (UART0_TX/I2C0_SDA/SPI0_RX/GP16)
BGP17: J8.19, U2.22 (UART0_RX/I2C0_SCL/SPI0_CSN/GP17)
BGP18: J8.17, U2.24 (I2C1_SDA/SPI0_SCK/GP18)
BGP19: J8.16, U2.25 (I2C1_SCL/SPI0_TX/GP19)
BGP20: J8.15, U2.26 (I2C0_SDA/GP20)
BGP21: J8.14, U2.27 (12C0_SCL/GP21)
BGP22: J8.12, U2.29 (GP22)
BGP26: J8.10, U2.31 (I2C1_SDA/ADC0/GP26)
BGP27: J8.9, U2.32 (I2C1_SCL/ADC1/GP27)
BGP28: J8.7, U2.34 (ADC2_GP28)
BRUN: J8.11, U2.30 (~RUN)
BVBUS: J8.1, U2.40 (VBUS)
BVSYS: J8.2, U2.39 (VSYS)
GND: J4.3, J4.8, J4.13, J4.18, J6.3, J6.8, J6.13, J6.18, J7.3, J7.8, J7.13, J7.18, J8.3, J8.8, J8.13, J8.18, U1.3 (GND), U1.8 (GND), U1.13 (GND), U1.18 (GND), U1.23 (GND), U1.28 (GND), U1.33 (AGND), U1.38 (GND), U1.F (GND), U2.3 (GND), U2.8 (GND), U2.13 (GND), U2.18 (GND), U2.23 (GND), U2.28 (GND), U2.33 (AGND), U2.38 (GND), U2.F (GND)
